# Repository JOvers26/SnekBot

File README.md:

# SnekBot

## Six-Axis Robotic Arm and Control System for ROAR Lunar Surface Operations
This project is a work in progress and setup is subject to change.

## Project Summary
SnekBot is a six-axis robotic arm designed for the QUT ROAR team to use in the Australian Rover Challenge (ARCh)

## Installation & Setup
### Initial Steps
Ensure Ubuntu 24.04 is flashed on the Raspberry Pi 5 and configured for remote access via SSH.

## ROS2 Jazzy
### **1. Set Locale**
Ensure your system uses **UTF-8** encoding:
```sh
locale  # Check for UTF-8

sudo apt update && sudo apt install locales
sudo locale-gen en_US en_US.UTF-8
sudo update-locale LC_ALL=en_US.UTF-8 LANG=en_US.UTF-8
export LANG=en_US.UTF-8

locale  # Verify settings
```

### **2. Enable Required Repositories**
```sh
sudo apt install software-properties-common
sudo add-apt-repository universe
```

### **3. Add ROS 2 GPG Key**
```sh
sudo apt update && sudo apt install curl -y
sudo curl -sSL https://raw.githubusercontent.com/ros/rosdistro/master/ros.key -o /usr/share/keyrings/ros-archive-keyring.gpg
```

### **4. Add ROS 2 Repository**
```sh
echo "deb [arch=$(dpkg --print-architecture) signed-by=/usr/share/keyrings/ros-archive-keyring.gpg] http://packages.ros.org/ros2/ubuntu $(. /etc/os-release && echo $UBUNTU_CODENAME) main" | sudo tee /etc/apt/sources.list.d/ros2.list > /dev/null
```

### **5. Install Development Tools (Optional)**
```sh
sudo apt update && sudo apt install ros-dev-tools
```

### **6. Update Repository Caches**
```sh
sudo apt update
```

### **7. Upgrade System**
```sh
sudo apt upgrade
```

### **8. Install ROS 2 Jazzy Base**
```sh
sudo apt install ros-jazzy-ros-base
```

### **9. Setup Environment**
Ensure ROS 2 is sourced correctly:
```sh
# Replace ".bash" with your shell if you're not using Bash
# Possible values: setup.bash, setup.sh, setup.zsh
source /opt/ros/jazzy/setup.bash
```
For more details, visit the [official ROS 2 documentation](https://docs.ros.org/en/jazzy/Installation/Ubuntu-Install-Debs.html).

## Setting up SnekBot Project
### **1. Clone the repository**
```sh
git clone https://github.com/JOvers26/SnekBot
cd ~/SnekBot
```

### **2. Install dependencies**
```sh
cd ~/SnekBot/ros2_ws
sudo rosdep init
rosdep update
rosdep install --from-paths src --ignore-src -r -y
```

### **3. Install FOXGLOVE Monitoring (Optional)**
```sh
source /opt/ros/jazzy/setup.bash
sudo apt install ros-$ROS_DISTRO-foxglove-bridge
```

### **4. Build the ROS2 Workspace:**
```sh
cd ~SnekBot/ros2_ws
colcon build --symlink-install
source install/setup.bash
```

## Setting up ESP-IDF
### **1. Install Prerequisites**
```sh
sudo apt-get install git wget flex bison gperf python3 python3-pip python3-venv cmake ninja-build ccache libffi-dev libssl-dev dfu-util libusb-1.0-0
```

### **2. Get ESP-IDF**
```sh
mkdir -p ~/esp
cd ~/esp
git clone -b v5.2.5 --recursive https://github.com/espressif/esp-idf.git
```

### **3. Set up the Tools**
```sh
cd ~/esp/esp-idf
./install.sh all
```

### **4. Set up the Environment Variables**
```sh
. $HOME/esp/esp-idf/export.sh
```

### **5. Configure ESP32S3**
```sh
cd ~SnekBot/ESP32_Code/int32_Publisher
pip3 install catkin_pkg lark-parser colcon-common-extensions empy==3.3.4
idf.py set-target esp32s3
idf.py menuconfig

#In micro-ROS Settings ->
  #Set micro-ROS-Agent IP
  #Set WiFi Credentials
```

### **6. Build and flash software**
```sh
idf.py build
idf.py -p /dev/ttyACM0 flash

# Note if this does not work you may need to add user to the dialout group
sudo usermod -aG dialout $USER

idf.py -p /dev/ttyACM0 flash
```

## Install VSCode on Ubuntu
### **1. Install Prerequisites**
```sh
sudo apt-get install wget gpg
wget -qO- https://packages.microsoft.com/keys/microsoft.asc | gpg --dearmor > packages.microsoft.gpg
sudo install -D -o root -g root -m 644 packages.microsoft.gpg /etc/apt/keyrings/packages.microsoft.gpg
echo "deb [arch=amd64,arm64,armhf signed-by=/etc/apt/keyrings/packages.microsoft.gpg] https://packages.microsoft.com/repos/code stable main" |sudo tee /etc/apt/sources.list.d/vscode.list > /dev/null
rm -f packages.microsoft.gpg
sudo apt install apt-transport-https
sudo apt update
sudo apt install code # or code-insiders
```

## Setting up Robotics Toolbox Python environment
### **1. Install Prerequisites**
```sh
sudo apt install python3-venv
cd ~SnekBot
python3 -m venv venv
source venv/bin/activate

pip3 install pygame
pip3 install setuptools
pip3 install roboticstoolbox-python
pip3 install "numpy<2"
```

## Useful Commands
### **Sourcing Ros2**
```sh
source /opt/ros/jazzy/setup.bash
```

### **Building micro-ROS-Agent**
```sh
cd ~SnekBot/ros2_ws
colcon build --symlink-install
source install/setup.bash
```
```sh
ros2 run micro_ros_agent micro_ros_agent udp4 --port 8888
```

### **Launching Foxglove Monitoring**
```sh
source /opt/ros/jazzy/setup.bash
ros2 run foxglove_bridge foxglove_bridge
```

### **Sourcing ESP-IDF**
```sh
. $HOME/esp/esp-idf/export.sh
```

### **Flashing and Monitoring ESP32-S3**
```sh
idf.py -p /dev/ttyACM0 flash
idf.py -p /dev/ttyACM0 monitor
```

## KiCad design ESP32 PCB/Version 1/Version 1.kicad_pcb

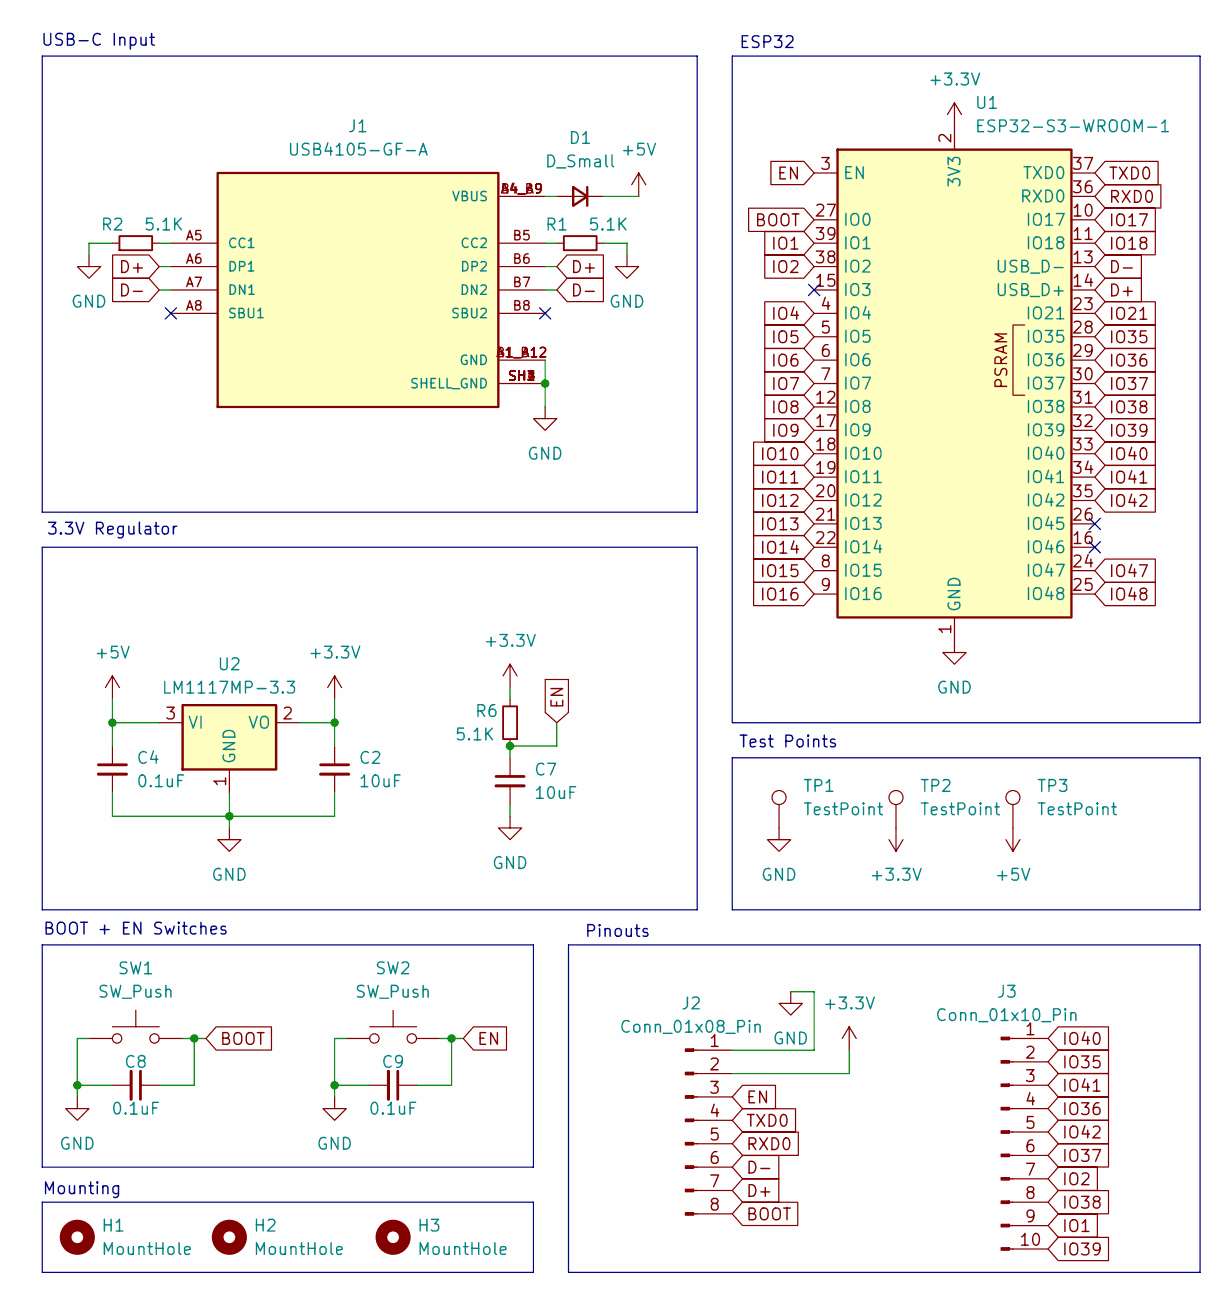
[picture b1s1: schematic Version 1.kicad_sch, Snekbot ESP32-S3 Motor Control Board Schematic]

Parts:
C2, C7: 10uF; C_0805_2012Metric_Pad1.18x1.45mm_HandSolder
C4, C8, C9: 0.1uF; C_0805_2012Metric_Pad1.18x1.45mm_HandSolder
D1: D_Small; D_0805_2012Metric_Pad1.15x1.40mm_HandSolder
H1, H2, H3: MountHole; MountingHole_3.2mm_M3
J1: USB4105-GF-A; GCT_USB4105-GF-A; PARTREV B4
J2: Conn_01x08_Pin; PinHeader_1x08_P2.54mm_Vertical
J3: Conn_01x10_Pin; PinHeader_2x05_P2.54mm_Vertical
R1, R2, R6: 5.1K; R_0805_2012Metric_Pad1.20x1.40mm_HandSolder
SW1, SW2: SW_Push; SW_Push_SPST_NO_Alps_SKRK
TP1, TP2, TP3: TestPoint; TestPoint_Pad_D3.0mm
U1: ESP32-S3-WROOM-1
U2: LM1117MP-3.3; SOT-223-3_TabPin2

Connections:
+3.3V: C2.1, J2.2, R6.2, TP2.1, U1.2 (3V3), U2.2 (VO)
+5V: C4.1, D1.1 (K), TP3.1, U2.3 (VI)
BOOT: C8.1, J2.8, SW1.2, U1.27 (IO0)
D+: J1.A6 (DP1), J1.B6 (DP2), J2.7, U1.14 (USB_D+)
D-: J1.A7 (DN1), J1.B7 (DN2), J2.6, U1.13 (USB_D-)
EN: C7.1, C9.1, J2.3, R6.1, SW2.2, U1.3 (EN)
GND: C2.2, C4.2, C7.2, C8.2, C9.2, J1.A1_B12 (GND), J1.B1_A12 (GND), J1.SH1 (SHELL_GND), J1.SH2 (SHELL_GND), J1.SH3 (SHELL_GND), J1.SH4 (SHELL_GND), J2.1, R1.2, R2.1, SW1.1, SW2.1, TP1.1, U1.1 (GND), U1.40 (GND), U1.41 (GND), U2.1 (GND)
IO1: J3.9, U1.39 (IO1)
IO2: J3.7, U1.38 (IO2)
IO4: U1.4 (IO4)
IO5: U1.5 (IO5)
IO6: U1.6 (IO6)
IO7: U1.7 (IO7)
IO8: U1.12 (IO8)
IO9: U1.17 (IO9)
IO10: U1.18 (IO10)
IO11: U1.19 (IO11)
IO12: U1.20 (IO12)
IO13: U1.21 (IO13)
IO14: U1.22 (IO14)
IO15: U1.8 (IO15)
IO16: U1.9 (IO16)
IO17: U1.10 (IO17)
IO18: U1.11 (IO18)
IO21: U1.23 (IO21)
IO35: J3.2, U1.28 (IO35)
IO36: J3.4, U1.29 (IO36)
IO37: J3.6, U1.30 (IO37)
IO38: J3.8, U1.31 (IO38)
IO39: J3.10, U1.32 (IO39)
IO40: J3.1, U1.33 (IO40)
IO41: J3.3, U1.34 (IO41)
IO42: J3.5, U1.35 (IO42)
IO47: U1.24 (IO47)
IO48: U1.25 (IO48)
unnamed: D1.2 (A), J1.A4_B9 (VBUS), J1.B4_A9 (VBUS)
unnamed: J1.A5 (CC1), R2.2
unnamed: J1.B5 (CC2), R1.1
RXD0: J2.5, U1.36 (RXD0)
TXD0: J2.4, U1.37 (TXD0)

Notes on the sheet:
BOOT + EN Switches
3.3V Regulator
Mounting
Pinouts
USB-C Input
ESP32
Test Points

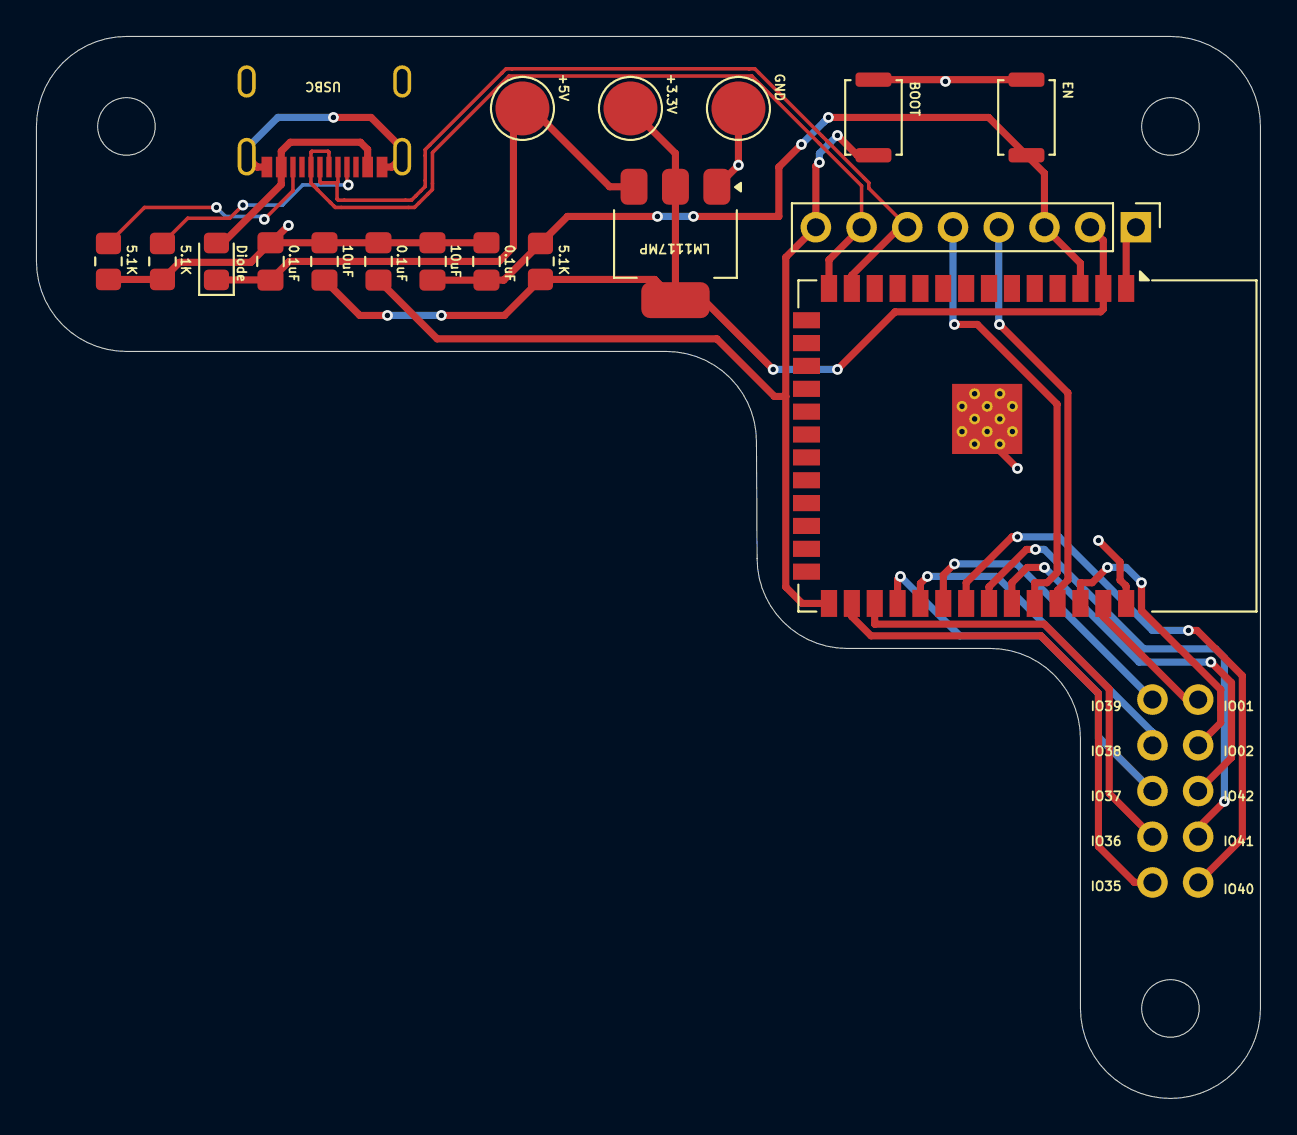
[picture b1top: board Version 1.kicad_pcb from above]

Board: 2 copper layers, 68.0 x 59.0 mm, 22 parts (0 on the bottom side), 22 nets.

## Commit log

2025-03-19 Installation Files
2025-03-20 install uninstall updates
2025-03-20 Directory rename
2025-03-20 Directory Updates
2025-03-20 build and venv
2025-03-20 remove files
2025-03-20 venv
2025-03-20 remove venv
2025-03-21 testing
2025-03-21 URDF
2025-03-27 restructure
2025-03-27 esp_components
2025-03-27 remove esp-idf
2025-03-29 structure updates
2025-03-30 add subscriber
2025-03-30 cJSON
2025-03-30 remove cJSON
2025-03-30 joint_states not working :(
2025-04-23 move launch files
2025-04-23 remove .sh files
2025-04-25 Webcam Streaming
2025-04-25 joint0 manipulation
2025-05-04 Removed code that is now invalid
